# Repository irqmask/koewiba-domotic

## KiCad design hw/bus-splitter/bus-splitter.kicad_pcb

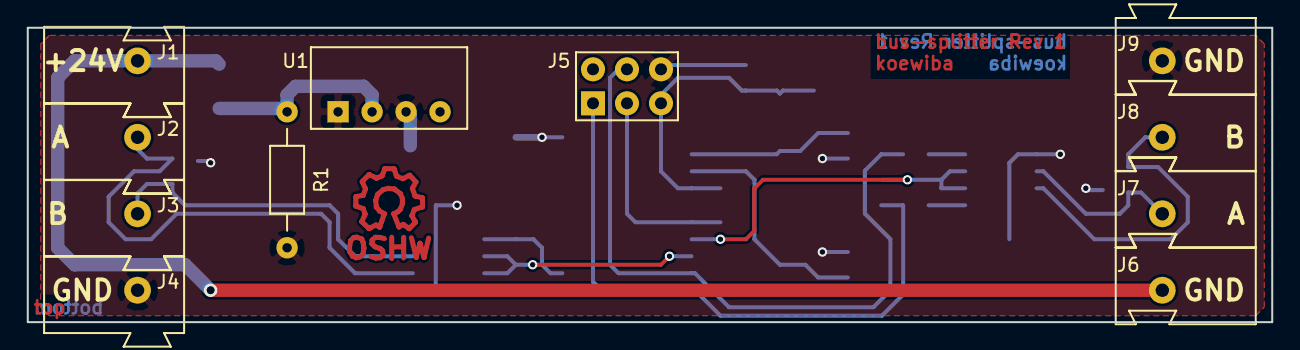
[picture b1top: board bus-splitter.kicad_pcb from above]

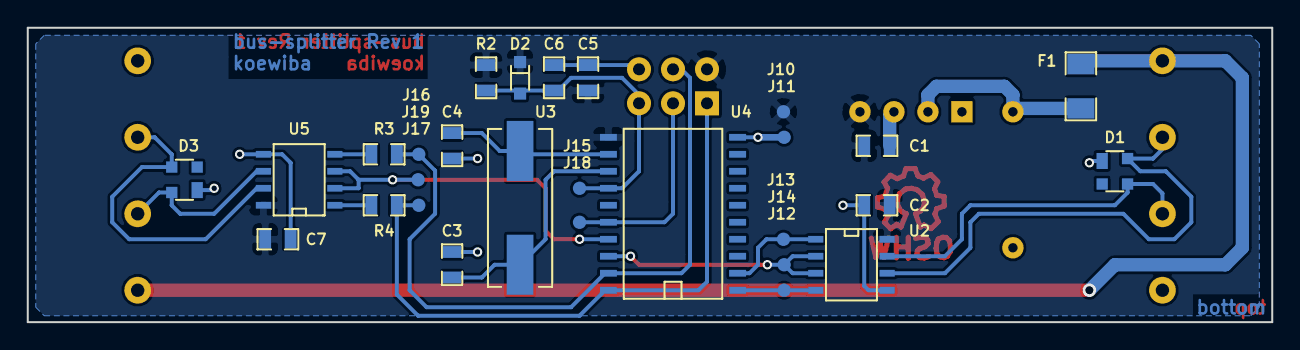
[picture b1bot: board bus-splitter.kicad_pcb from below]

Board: 2 copper layers, 93.0 x 22.0 mm, 40 parts (28 on the bottom side), 20 nets.

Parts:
C1: 100µF/6V; C_0805
C2, C5, C7: 100nF; C_0805
C3, C4: 18pF; C_0805
C6: 4,7nF; C_0805
D1, D3: SEMTECH_SR05; D_SOT143
D2: 1N4148; D_SOD323
F1: 0,15A; R_1206
J1, J6: WAGO 243-723; WAGO243
J2, J7: WAGO 243-724; WAGO243
J3, J8: WAGO 243-721; WAGO243
J4, J9: WAGO 243-722; WAGO243
J5: CONN-ISP-6; HEADER_3x2
J10: tp_vcc; Testpoint_1mm
J11: tp_gnd; Testpoint_1mm
J12: tp_txd0; Testpoint_1mm
J13: tp_rxd0; Testpoint_1mm
J14: tp_txden0; Testpoint_1mm
J15: tp_reset; Testpoint_1mm
J16: tp_txd1_mosi; Testpoint_1mm
J17: tp_rxd1_miso; Testpoint_1mm
J18: tp_sck; Testpoint_1mm
J19: tp_txden1; Testpoint_1mm
LOGO1: OPEN_HARDWARE_1; Symbol_OSHW-Logo_Copper
R1: Varistor; R_RM10.16mm
R2: 10k; R_0805
R3, R4: 100; R_0805
U1: AM1S-2405; AM1S-XXXX_SIL4
U2, U5: MAX487; SO8E
U3: 7.3728MHz; CRY_HC49_SMD
U4: ATTINY1634-SOIC; SO20L

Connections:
+24V: F1.1, R1.1, U1.2
/24V_UNFUSED: F1.2, J1.1, J6.1
//RESET: C6.1, D2.1, J5.5, J15.1, R2.2, U4.14
/A0: D1.4, J2.1, U2.6
/A1: D3.4, J7.1, U5.6
/B0: D1.3, J3.1, U2.7
/B1: D3.3, J8.1, U5.7
/RXD0: J13.1, U2.1, U4.2
/RXD1_MISO: J5.1, J17.1, R4.1, U4.20
/SCK: J5.3, J18.1, U4.16
/TXD0: J12.1, U2.4, U4.1
/TXD1_MOSI: J5.4, J16.1, R3.1, U4.19
/TXDEN0: J14.1, U2.2, U2.3, U4.18
/TXDEN1: J19.1, U4.17, U5.2, U5.3
GND: C1.2, C2.1, C3.2, C4.2, C5.1, C6.2, C7.1, D1.1, D3.1, J4.1, J5.6, J9.1, J11.1, R1.2, U1.1, U1.3, U2.5, U4.10, U5.5
unnamed: C3.1, U3.2, U4.13
unnamed: C4.1, U3.1, U4.12
unnamed: R3.2, U5.4
unnamed: R4.2, U5.1
VCC: C1.1, C2.2, C5.2, C7.2, D2.2, J5.2, J10.1, R2.1, U1.4, U2.8, U4.11, U5.8

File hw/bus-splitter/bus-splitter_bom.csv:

"Id";"Bezeichner";"Gehäuse";"Stückzahl";"Bezeichnung";"Anbieter und Ref";
1;"U1";"AM1S-XXXX_SIL4";1;"AM1S-2405";;;
2;"J1,J6";"WAGO243";2;"WAGO 243-723";;;
3;"J2,J7";"WAGO243";2;"WAGO 243-724";;;
4;"J3,J8";"WAGO243";2;"WAGO 243-721";;;
5;"J4,J9";"WAGO243";2;"WAGO 243-722";;;
6;"C1";"C_0805";1;"100µF/6V";;;
7;"C2,C5,C7";"C_0805";3;"100nF";;;
8;"C3,C4";"C_0805";2;"18pF";;;
9;"C6";"C_0805";1;"4,7nF";;;
10;"D1,D3";"D_SOT143";2;"SEMTECH_SR05";;;
11;"D2";"D_SOD323";1;"1N4148";;;
12;"F1";"R_1206";1;"0,15A";;;
13;"J5";"HEADER_3x2";1;"CONN-ISP-6";;;
14;"R1";"R_RM10.16mm";1;"Varistor";;;
15;"R2";"R_0805";1;"10k";;;
16;"R3,R4";"R_0805";2;"100";;;
17;"U2,U5";"SO8E";2;"MAX487";;;
18;"U3";"CRY_HC49_SMD";1;"7.3728MHz";;;
19;"U4";"SO20L";1;"ATTINY1634-SOIC";;;
20;"LOGO1";"Symbol_OSHW-Logo_Copper";1;"OPEN_HARDWARE_1";;;
21;"J10";"Testpoint_1mm";1;"tp_vcc";;;
22;"J11";"Testpoint_1mm";1;"tp_gnd";;;
23;"J12";"Testpoint_1mm";1;"tp_txd0";;;
24;"J13";"Testpoint_1mm";1;"tp_rxd0";;;
25;"J14";"Testpoint_1mm";1;"tp_txden0";;;
26;"J15";"Testpoint_1mm";1;"tp_reset";;;
27;"J16";"Testpoint_1mm";1;"tp_txd1_mosi";;;
28;"J17";"Testpoint_1mm";1;"tp_rxd1_miso";;;
29;"J18";"Testpoint_1mm";1;"tp_sck";;;
30;"J19";"Testpoint_1mm";1;"tp_txden1";;;

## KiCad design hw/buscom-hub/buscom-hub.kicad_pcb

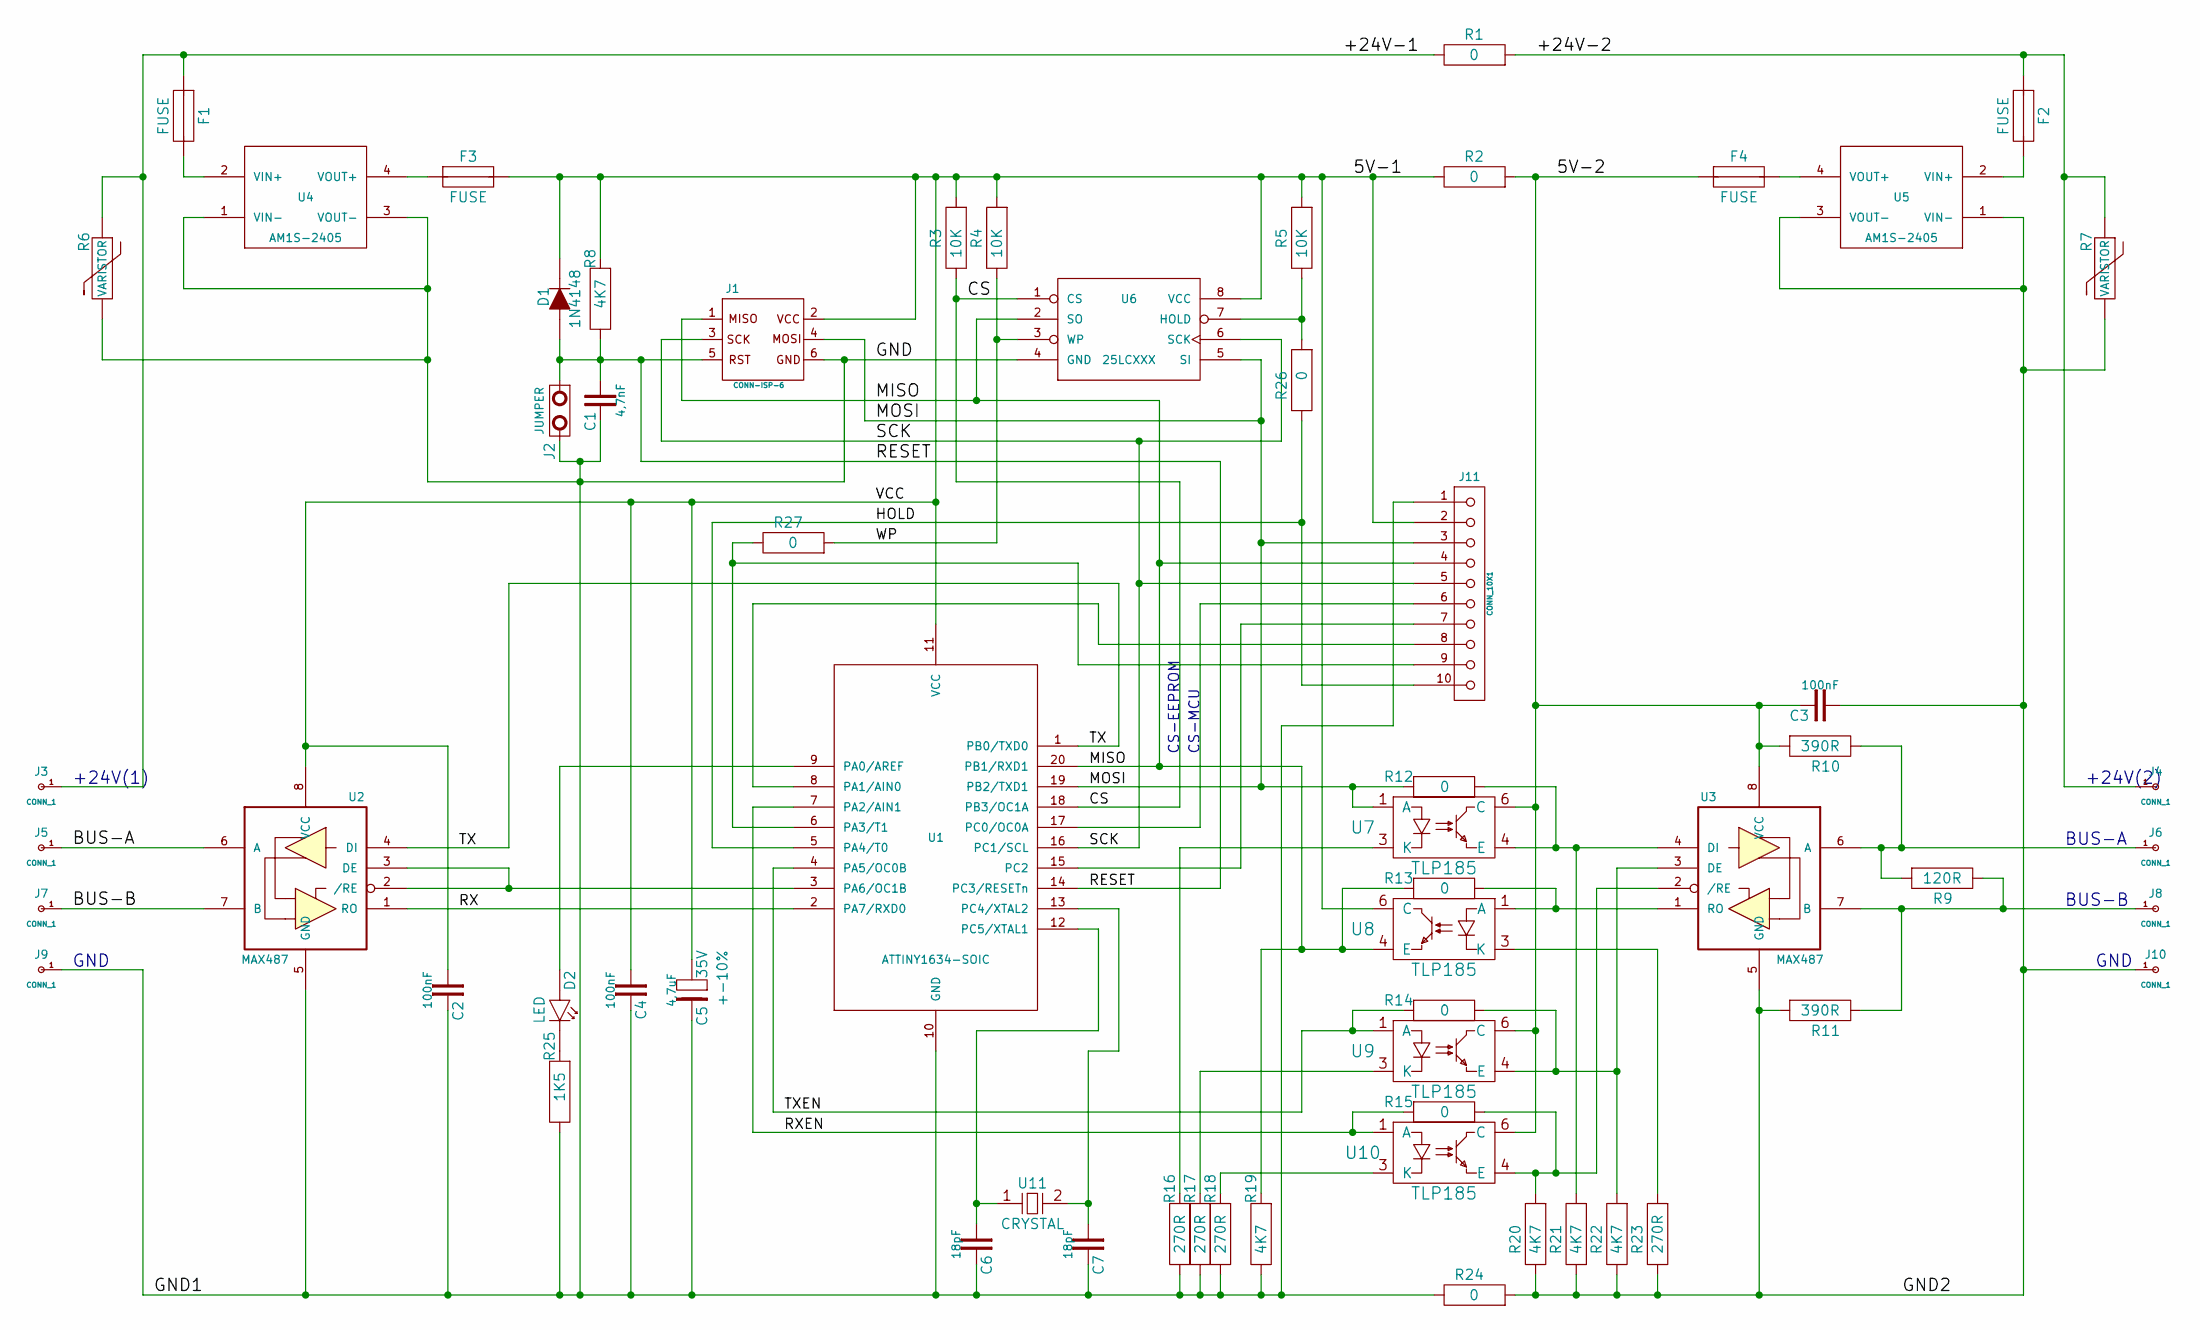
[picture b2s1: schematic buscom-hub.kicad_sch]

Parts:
C1: 4,7nF
C2, C3, C4: 100nF
C5: 4,7uF; 35V
C6, C7: 18pF
D1: 1N4148
D2: LED
F1, F2, F3, F4: FUSE
J1: CONN-ISP-6; AVR-ISP-6
J2: JUMPER
J3, J4, J5, J6, J7, J8, J9, J10: CONN_1
J11: CONN_10X1
R1, R2, R12, R13, R14, R15, R24, R26, R27: 0
R3, R4, R5: 10K
R6, R7: VARISTOR
R8, R19, R20, R21, R22: 4K7
R9: 120R
R10, R11: 390R
R16, R17, R18, R23: 270R
R25: 1K5
U1: ATTINY1634-SOIC; SO20L
U2, U3: MAX487; SSOP28
U4, U5: AM1S-2405; AM1S-XXXX_SIL4
U6: 25LCXXX; SO8N
U7, U8, U9, U10: TLP185
U11: CRYSTAL

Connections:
/5V-2: C3.2, F4.1, R2.1, R10.1, U3.8 (VCC), U7.6 (C), U9.6 (C), U10.6 (C)
/+24V-1: F1.1, J3.1, R1.2, R6.1
/+24V-2: F2.1, J4.1, R1.1, R7.1
/BUS-A: J5.1, U2.6 (A)
/BUS-B: J7.1, U2.7 (B)
/CS: R3.2, U1.18 (PB3/OC1A), U6.1 (CS)
/GND1: C1.2, C2.2, C4.1, C5.2, C6.2, C7.2, J1.6, J2.2, J9.1, J11.1, R6.2, R16.2, R17.2, R18.2, R19.2, R24.2, R25.2, U1.10 (GND), U2.5 (GND), U4.1 (VIN-), U4.3 (VOUT-), U6.4 (GND)
/GND2: C3.1, J10.1, R7.2, R11.1, R20.2, R21.2, R22.2, R23.2, R24.1, U3.5 (GND), U5.1 (VIN-), U5.3 (VOUT-)
/HOLD: J11.10, R26.2, U1.5 (PA4/T0)
/MISO: J1.1, J11.4, R13.1, R19.1, U1.20 (PB1/RXD1), U6.2 (SO), U8.4 (E)
/MOSI: J1.4, J11.3, R12.1, U1.19 (PB2/TXD1), U6.5 (SI), U7.1 (A)
/RESET: C1.1, D1.1 (A), J1.5, J2.1, R8.2, U1.14 (PC3/RESETn)
/RX: U1.2 (PA7/RXD0), U2.1 (RO)
/RXEN: R15.1, U1.7 (PA2/AIN1), U10.1 (A)
/SCK: J1.3, J11.5, U1.16 (PC1/SCL), U6.6 (SCK)
/TX: U1.1 (PB0/TXD0), U2.4 (DI)
/TXEN: R14.1, U1.4 (PA5/OC0B), U9.1 (A)
/VCC: C2.1, C4.2, C5.1, D1.2 (C), F3.2, J1.2, J11.2, R2.2, R3.1, R4.1, R5.1, R8.1, U1.11 (VCC), U2.8 (VCC), U6.8 (VCC), U8.6 (C)
/WP: R4.2, R27.1, U6.3 (WP)
unnamed: F4.2, U5.4 (VOUT+)
unnamed: D2.2 (C), R25.1
unnamed: J11.8, U1.8 (PA1/AIN0)
unnamed: R14.2, R22.1, U3.3 (DE), U9.4 (E)
unnamed: R18.1, U10.3 (K)
unnamed: R15.2, R20.1, U3.2 (/RE), U10.4 (E)
unnamed: D2.1 (A), U1.9 (PA0/AREF)
unnamed: F1.2, U4.2 (VIN+)
unnamed: F2.2, U5.2 (VIN+)
unnamed: J8.1, R9.2, R11.2, U3.7 (B)
unnamed: C6.1, U1.12 (PC5/XTAL1), U11.1
unnamed: F3.1, U4.4 (VOUT+)
unnamed: R17.1, U9.3 (K)
unnamed: R16.1, U7.3 (K)
unnamed: R23.1, U8.3 (K)
unnamed: J11.6, U1.17 (PC0/OC0A)
unnamed: J11.7, U1.15 (PC2)
unnamed: R12.2, R21.1, U3.4 (DI), U7.4 (E)
unnamed: R5.2, R26.1, U6.7 (HOLD)
unnamed: J11.9, R27.2, U1.6 (PA3/T1)
unnamed: R13.2, U3.1 (RO), U8.1 (A)
unnamed: C7.1, U1.13 (PC4/XTAL2), U11.2
unnamed: U1.3 (PA6/OC1B), U2.2 (/RE), U2.3 (DE)
unnamed: J6.1, R9.1, R10.2, U3.6 (A)

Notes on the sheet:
GND
CS-EEPROM
CS-MCU
BUS-A
BUS-B
+24V(2)
+24V(1)

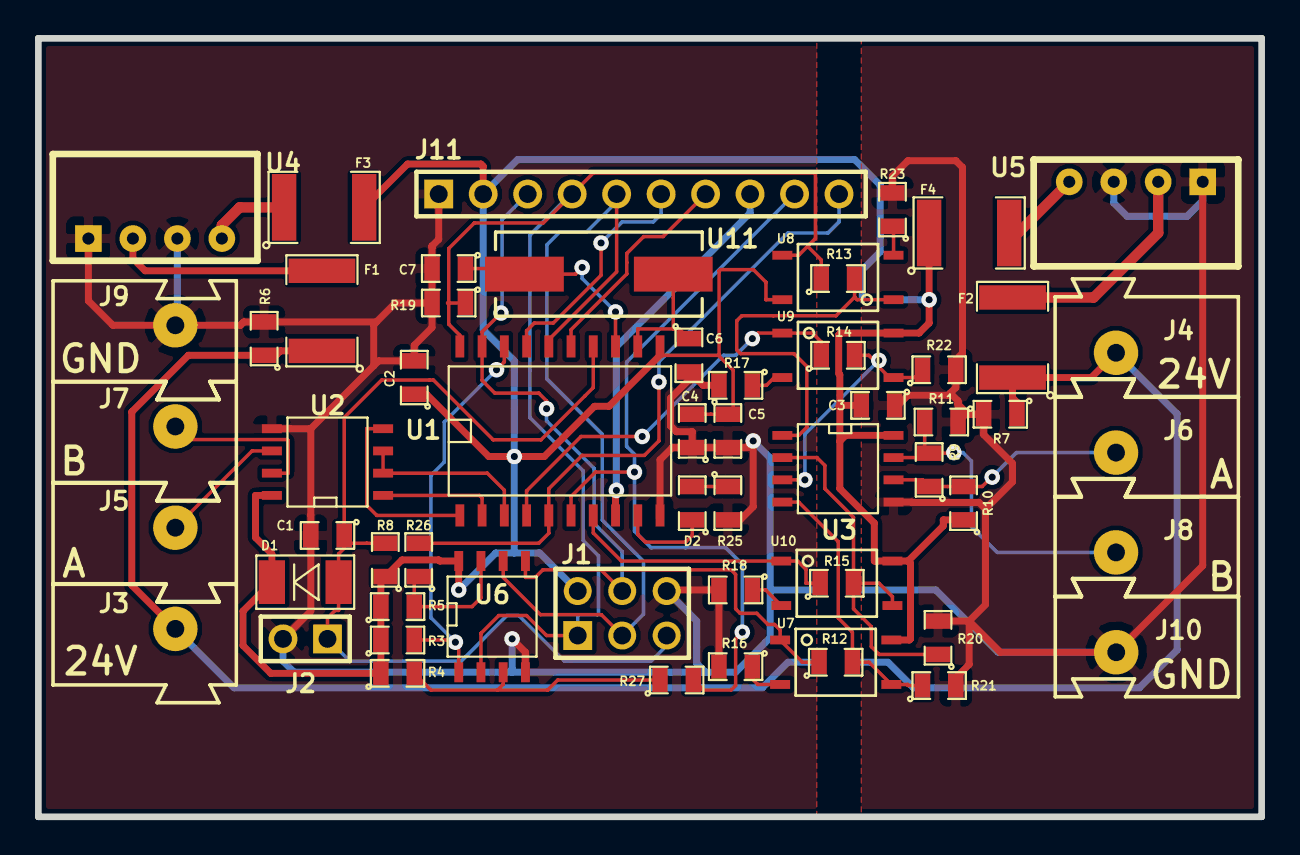
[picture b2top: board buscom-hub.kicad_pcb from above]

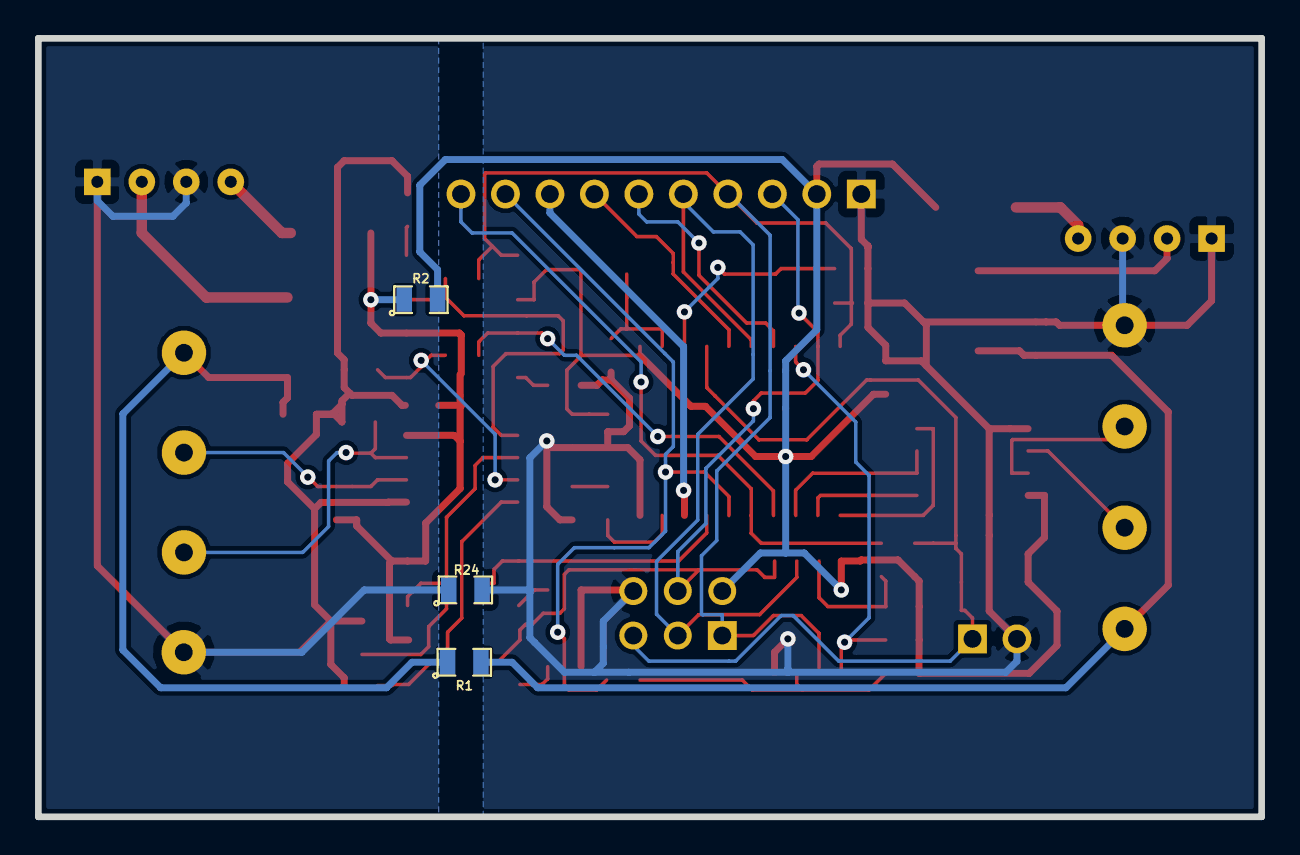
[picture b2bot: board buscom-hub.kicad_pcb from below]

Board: 2 copper layers, 69.8 x 44.4 mm, 62 parts (3 on the bottom side), 43 nets.

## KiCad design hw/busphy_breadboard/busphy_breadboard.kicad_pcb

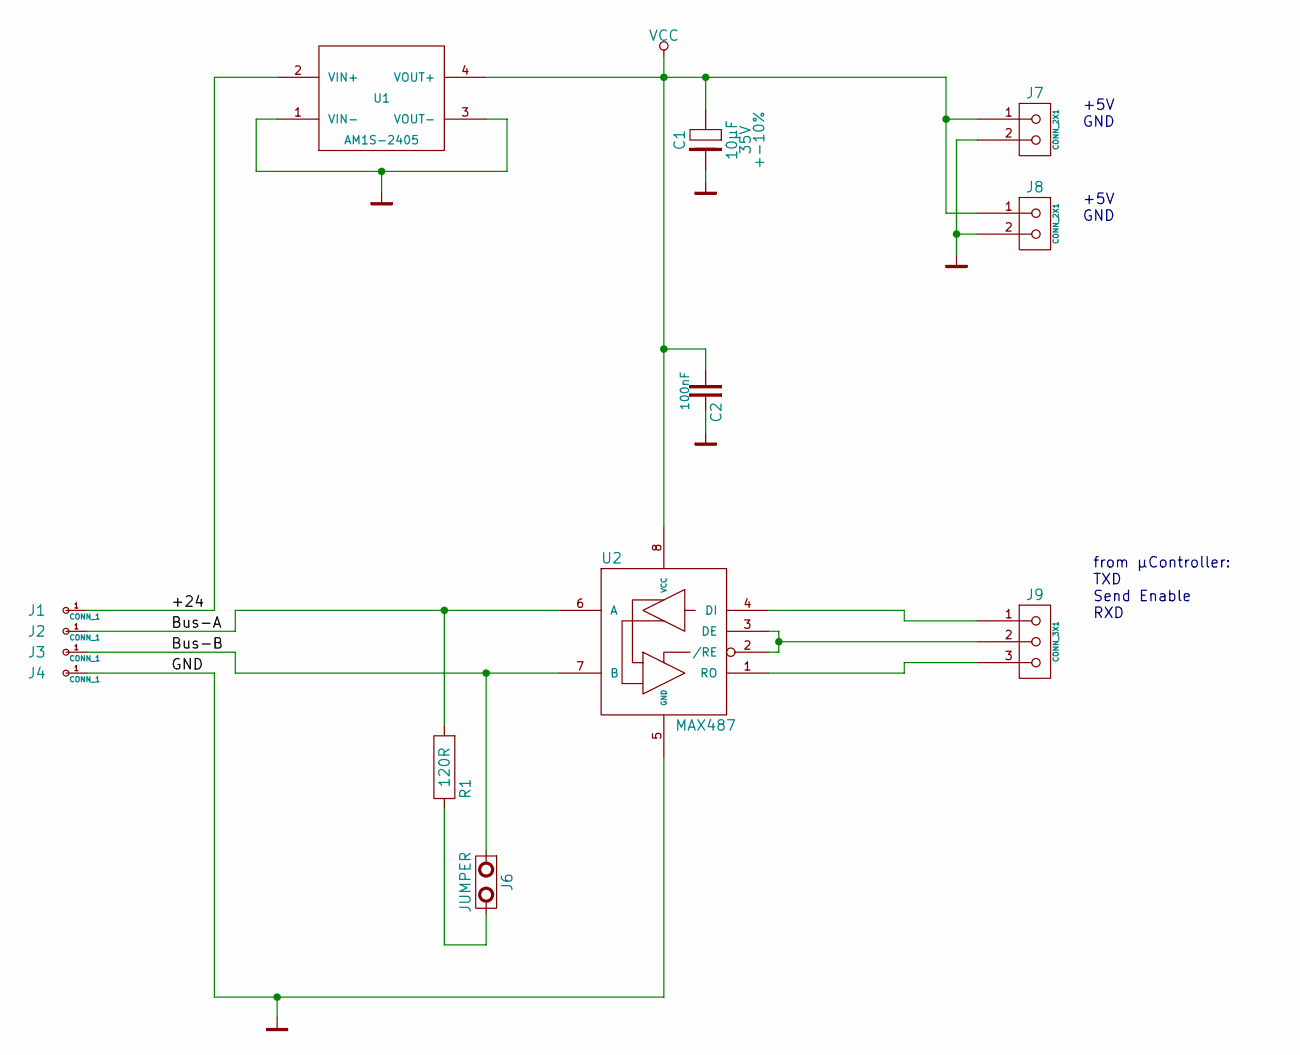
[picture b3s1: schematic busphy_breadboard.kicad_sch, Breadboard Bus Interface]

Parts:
C1: 10µF; Voltage 35V
C2: 100nF
J1, J2, J3, J4: CONN_1
J6: JUMPER
J7, J8: CONN_2X1
J9: CONN_3X1
R1: 120R
U1: AM1S-2405; AM1S-XXXX_SIL4
U2: MAX487; SSOP28

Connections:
/+24: J1.1, U1.2 (VIN+)
/Bus-A: J2.1, R1.1, U2.6 (A)
/Bus-B: J3.1, J6.1, U2.7 (B)
GND: C1.2, C2.2, J4.1, J7.2, J8.2, U1.1 (VIN-), U1.3 (VOUT-), U2.5 (GND)
unnamed: J9.2, U2.2 (/RE), U2.3 (DE)
unnamed: J9.3, U2.1 (RO)
unnamed: J9.1, U2.4 (DI)
unnamed: J6.2, R1.2
VCC: C1.1, C2.1, J7.1, J8.1, U1.4 (VOUT+), U2.8 (VCC)

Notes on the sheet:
from µController: TXD Send Enable RXD
+5V GND

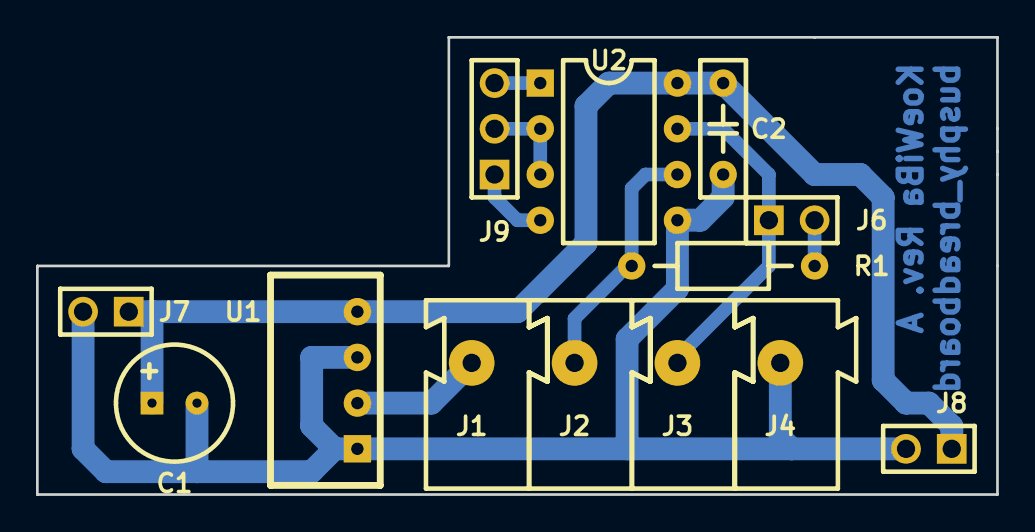
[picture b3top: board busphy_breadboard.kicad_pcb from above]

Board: 2 copper layers, 53.3 x 25.4 mm, 13 parts (0 on the bottom side), 9 nets.

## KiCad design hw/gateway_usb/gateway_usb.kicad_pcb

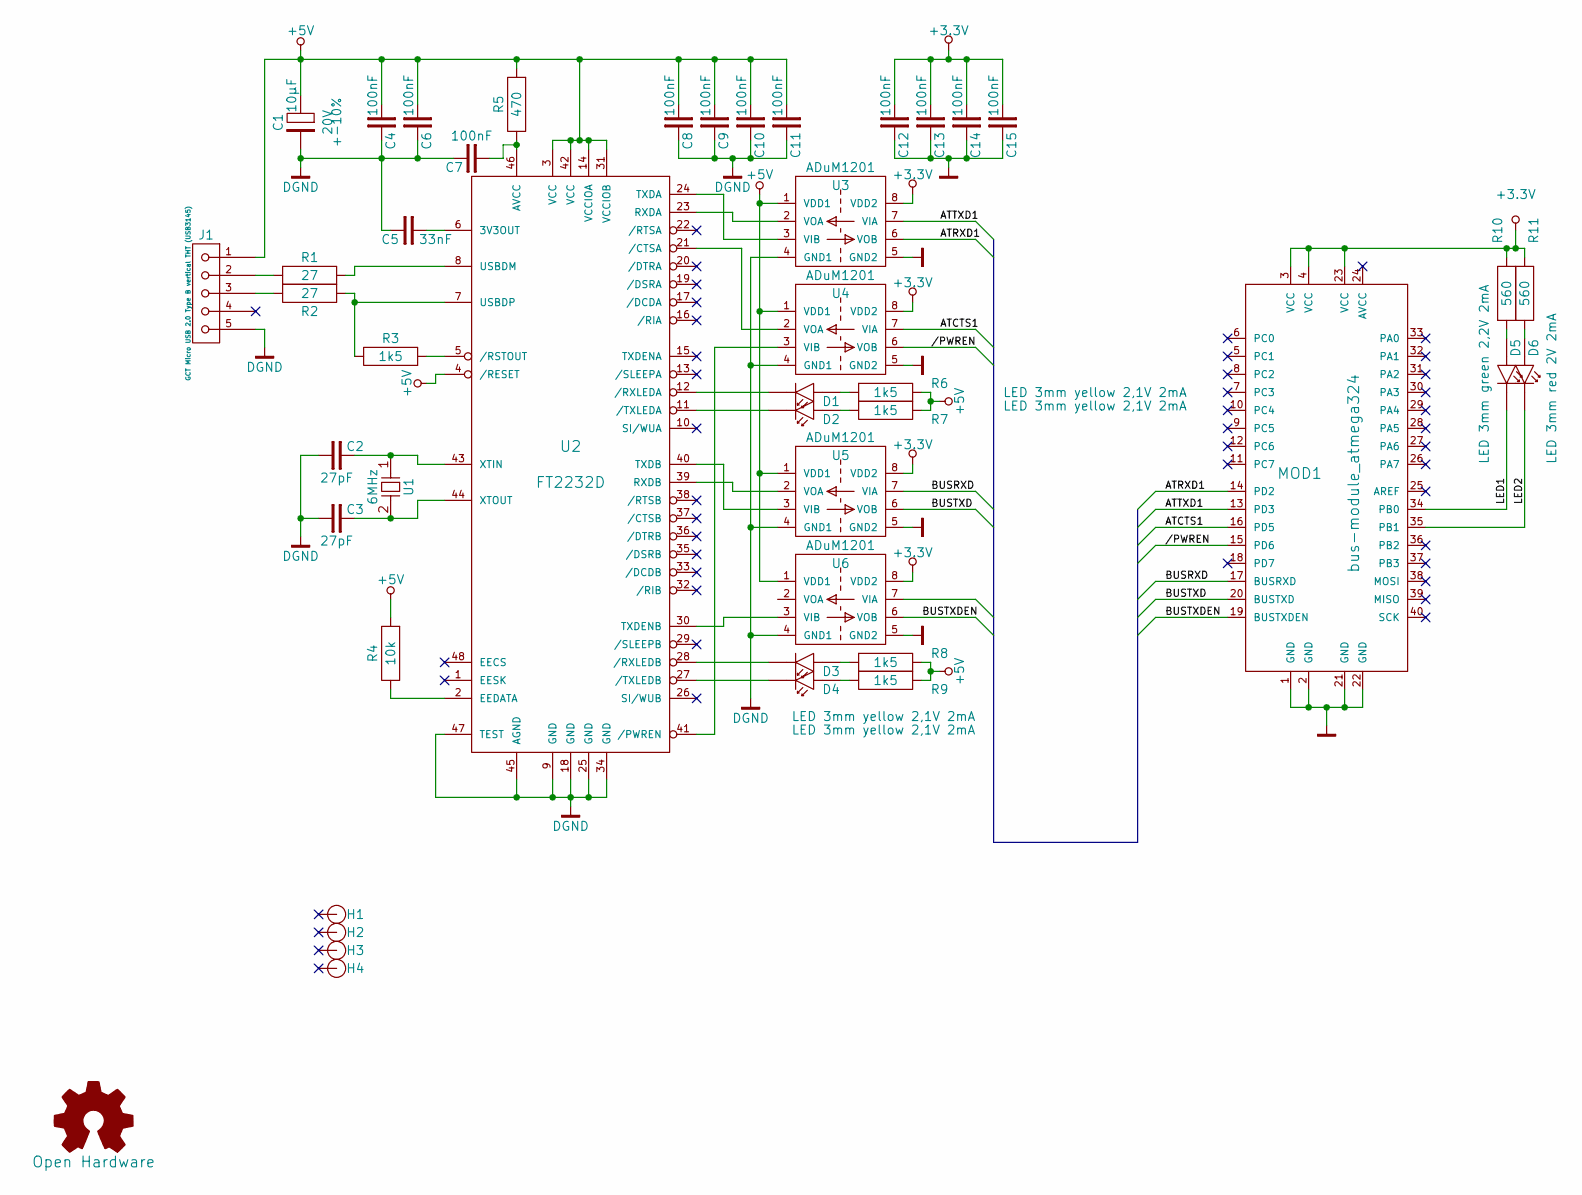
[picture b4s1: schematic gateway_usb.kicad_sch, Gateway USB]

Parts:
C1: 10µF; cp_smd_6.3; Voltage 20V
C2, C3: 27pF; SM0805
C4, C6, C7, C8, C9, C10, C11, C12, C13, C14, C15: 100nF; SM0805
C5: 33nF; SM0805
D1, D2, D3, D4: LED 3mm yellow 2,1V 2mA; LED_3MM
D5: LED 3mm green 2,2V 2mA; LED_3MM
D6: LED 3mm red 2V 2mA; LED_3MM
H1, H2, H3, H4: HOLE; HOLE_3.5x7mm
J1: GCT Micro USB 2.0 Type B vertical THT (USB3145); USB2.0_micro_THT_vertical_GCT_USB3145
LOGO1: Open Hardware; Symbol_OSHW-Logo_SilkScreen
MOD1: bus-module_atmega324
R1, R2: 27; SM0805
R3, R6, R7, R8, R9: 1k5; SM0805
R4: 10k; SM0805
R5: 470; SM0805
R10, R11: 560; SM0805
U1: 6MHz; HC49-SMD
U2: FT2232D; LQFP-48_7x7mm_Pitch0.5mm
U3, U4, U5, U6: ADuM1201; SO8E

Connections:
+3.3V: C12.1, C13.1, C14.1, C15.1, MOD1.3 (VCC), MOD1.4 (VCC), MOD1.23 (VCC), R10.2, R11.2, U3.8 (VDD2), U4.8 (VDD2), U5.8 (VDD2), U6.8 (VDD2)
+5V: C1.1, C4.1, C6.1, C8.1, C9.1, C10.1, C11.1, J1.1, R4.1, R5.1, R6.2, R7.2, R8.2, R9.2, U2.3 (VCC), U2.4 (/RESET), U2.14 (VCCIOA), U2.31 (VCCIOB), U2.42 (VCC), U3.1 (VDD1), U4.1 (VDD1), U5.1 (VDD1), U6.1 (VDD1)
//PWREN: MOD1.15 (PD6), U4.6 (VOB)
/ATCTS1: MOD1.16 (PD5), U4.7 (VIA)
/ATRXD1: MOD1.14 (PD2), U3.6 (VOB)
/ATTXD1: MOD1.13 (PD3), U3.7 (VIA)
/BUSRXD: MOD1.17 (BUSRXD), U5.7 (VIA)
/BUSTXD: MOD1.20 (BUSTXD), U5.6 (VOB)
/BUSTXDEN: MOD1.19 (BUSTXDEN), U6.6 (VOB)
/LED1: D5.2 (C), MOD1.34 (PB0)
/LED2: D6.2 (C), MOD1.35 (PB1)
DGND: C1.2, C2.1, C3.1, C4.2, C5.2, C6.2, C7.1, C8.2, C9.2, C10.2, C11.2, J1.5, U2.9 (GND), U2.18 (GND), U2.25 (GND), U2.34 (GND), U2.45 (AGND), U2.47 (TEST), U3.4 (GND1), U4.4 (GND1), U5.4 (GND1), U6.4 (GND1)
GND: C12.2, C13.2, C14.2, C15.2, MOD1.1 (GND), MOD1.2 (GND), MOD1.21 (GND), MOD1.22 (GND), U3.5 (GND2), U4.5 (GND2), U5.5 (GND2), U6.5 (GND2)
unnamed: C2.2, U1.1, U2.43 (XTIN)
unnamed: C3.2, U1.2, U2.44 (XTOUT)
unnamed: C5.1, U2.6 (3V3OUT)
unnamed: C7.2, R5.2, U2.46 (AVCC)
unnamed: D1.1 (A), R6.1
unnamed: D1.2 (C), U2.12 (/RXLEDA)
unnamed: D2.1 (A), R7.1
unnamed: D2.2 (C), U2.11 (/TXLEDA)
unnamed: D3.1 (A), R8.1
unnamed: D3.2 (C), U2.28 (/RXLEDB)
unnamed: D4.1 (A), R9.1
unnamed: D4.2 (C), U2.27 (/TXLEDB)
unnamed: D5.1 (A), R10.1
unnamed: D6.1 (A), R11.1
unnamed: J1.2, R1.1
unnamed: J1.3, R2.1
unnamed: R1.2, U2.8 (USBDM)
unnamed: R2.2, R3.2, U2.7 (USBDP)
unnamed: R3.1, U2.5 (/RSTOUT)
unnamed: R4.2, U2.2 (EEDATA)
unnamed: U2.21 (/CTSA), U4.2 (VOA)
unnamed: U2.23 (RXDA), U3.2 (VOA)
unnamed: U2.24 (TXDA), U3.3 (VIB)
unnamed: U2.30 (TXDENB), U6.3 (VIB)
unnamed: U2.39 (RXDB), U5.2 (VOA)
unnamed: U2.40 (TXDB), U5.3 (VIB)
unnamed: U2.41 (/PWREN), U4.3 (VIB)

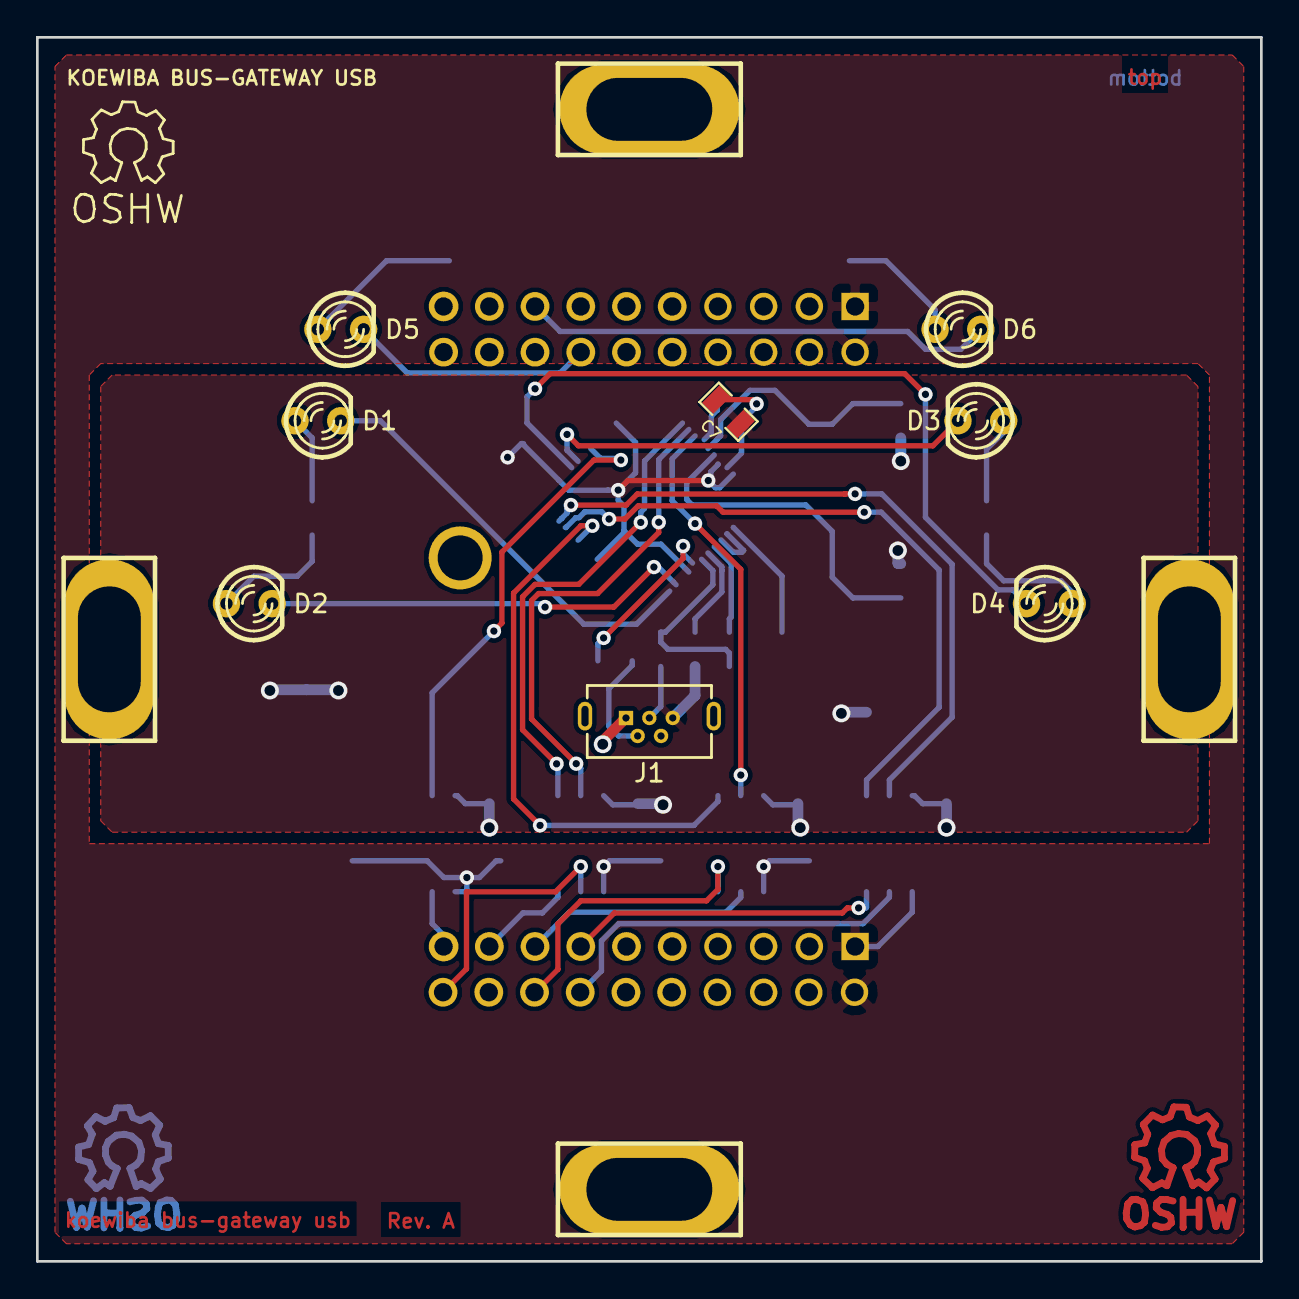
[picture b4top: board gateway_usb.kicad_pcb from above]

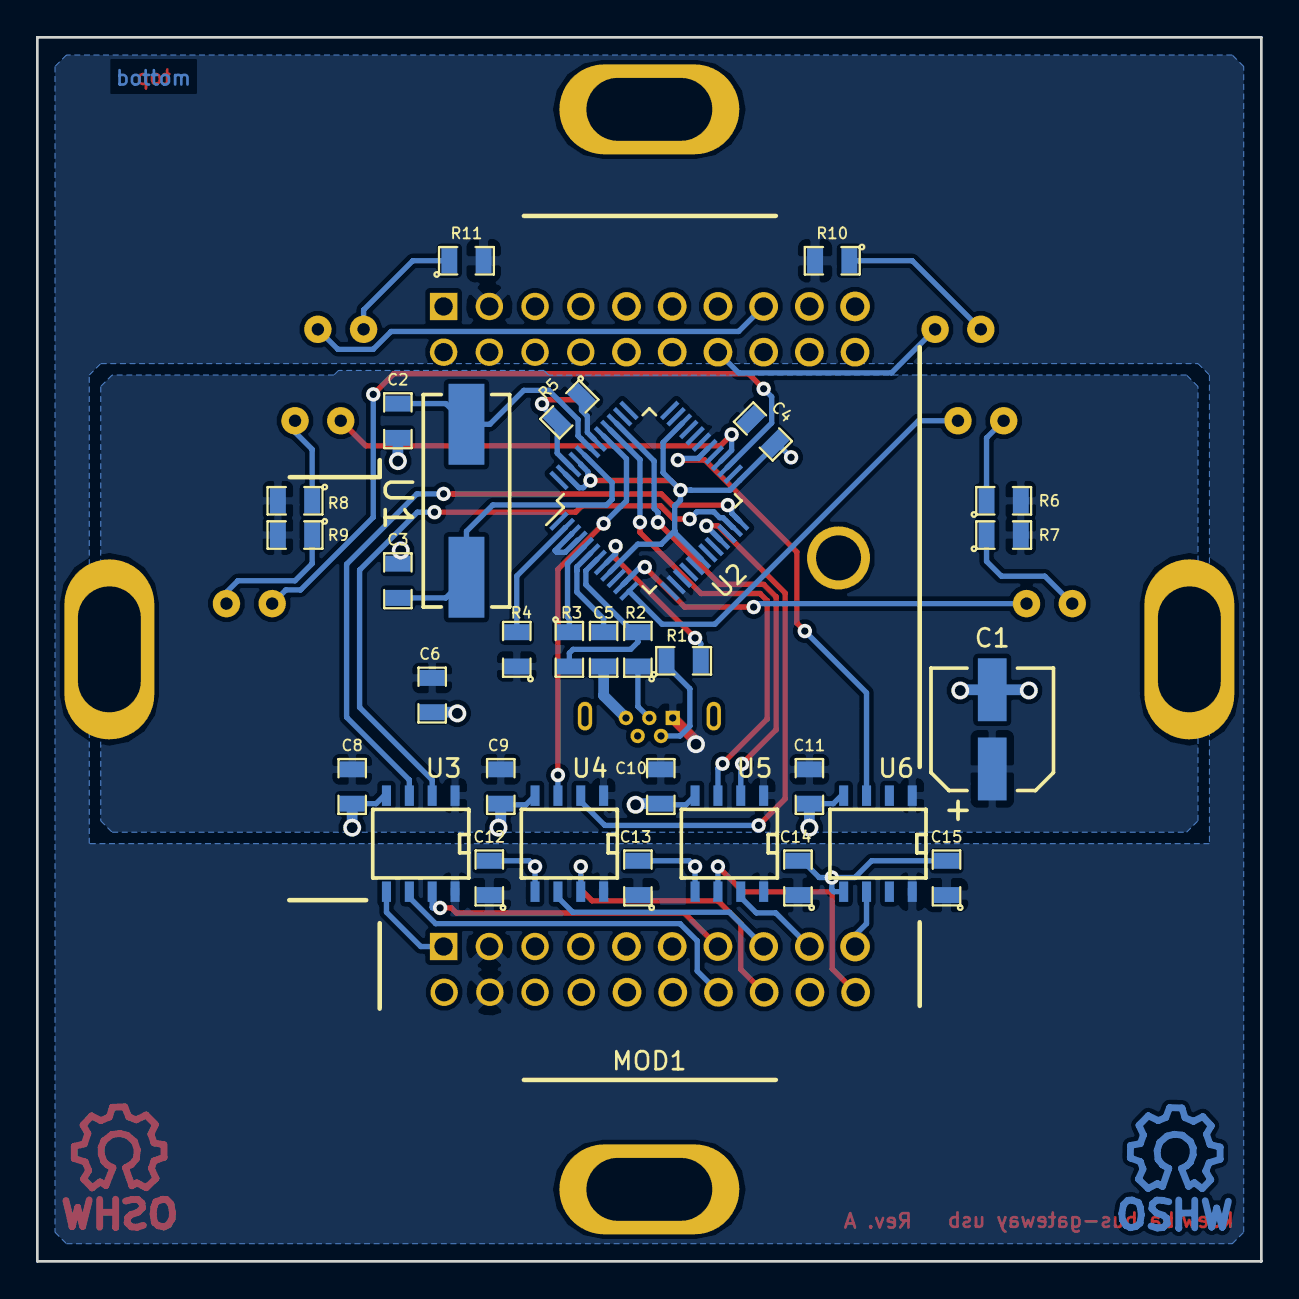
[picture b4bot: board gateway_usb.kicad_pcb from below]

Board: 2 copper layers, 68.0 x 68.0 mm, 47 parts (33 on the bottom side), 40 nets.

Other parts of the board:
LOGO1#2, LOGO1#3: Open Hardware; Symbol_OSHW-Logo_Copper

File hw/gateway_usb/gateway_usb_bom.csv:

Bezeichner,Gehäuse,Stückzahl,Bezeichnung,Anbieter und Ref
C1,cp_smd_6.3,1,10µF,
"C4,C6,C7,C8,C9,C10,C11,C12,C13,C14,C15",SM0805,4,100nF,
"C2,C3",SM0805,2,27pF,
C5,SM0805,1,33nF,
"D1,D2,D3,D4",LED_3MM,4,"LED 3mm yellow 2,1V 2mA",
D5,LED_3MM,1,"LED 3mm green 2,2V 2mA",
D6,LED_3MM,1,LED 3mm red 2V 2mA,
J1,USB2.0_micro_THT_vertical_GCT_USB3145,1,GCT Micro USB 2.0 Type B vertical THT (USB3145),
MOD1,bus-module_atmega324,1,bus-module_atmega324,
"R1,R2",SM0805,2,27,
"R10,R11",SM0805,2,560,
"R3,R6,R7,R8,R9",SM0805,5,1k5,
R4,SM0805,1,10k,
R5,SM0805,1,470,
U1,HC49-SMD,1,6MHz,
U2,LQFP-48_7x7mm_Pitch0.5mm,1,FT2232D,
"U3,U4,U5,U6",SO8E,4,ADuM1201,

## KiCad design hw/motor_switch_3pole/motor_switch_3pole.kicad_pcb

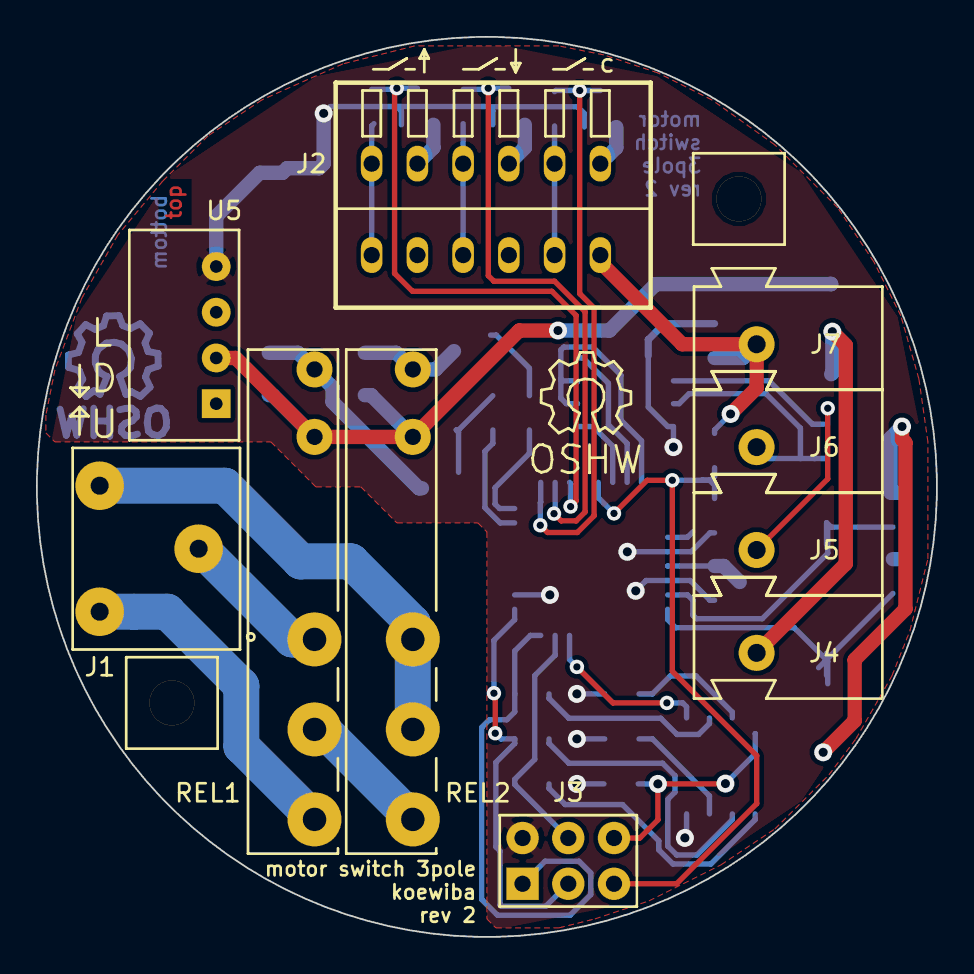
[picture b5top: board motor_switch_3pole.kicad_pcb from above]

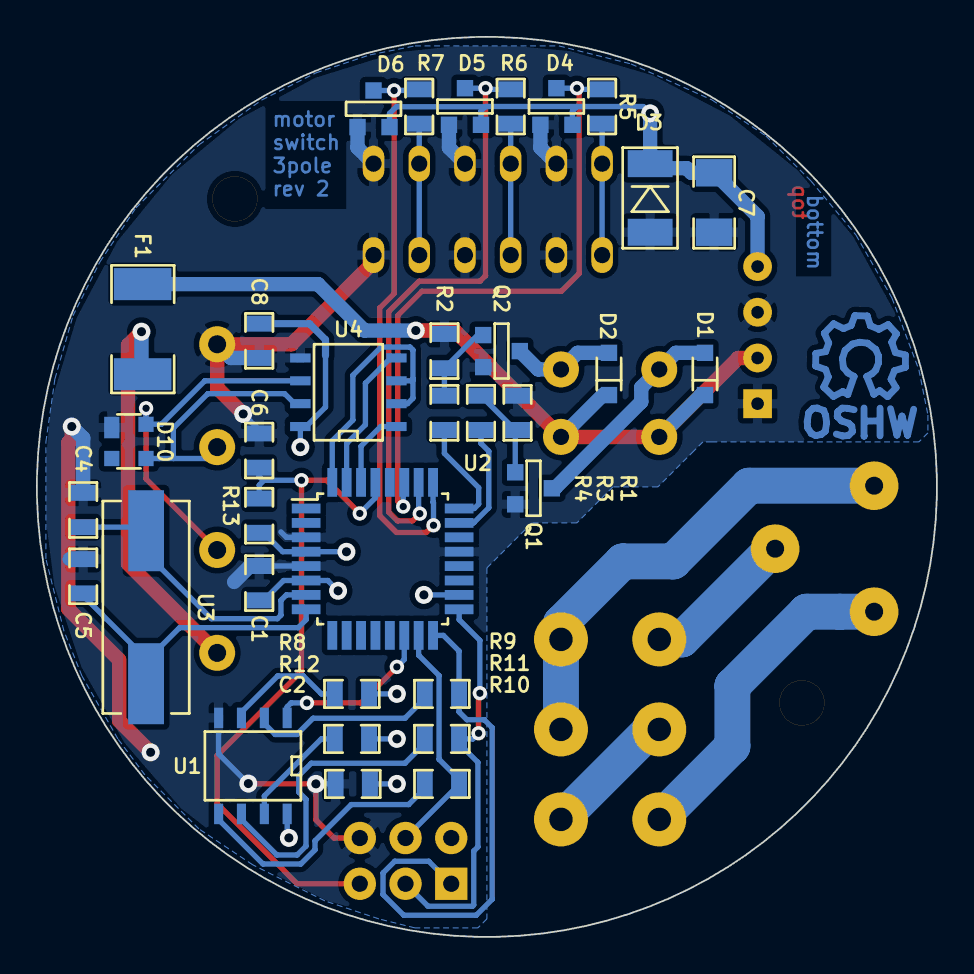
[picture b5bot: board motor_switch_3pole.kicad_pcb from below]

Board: 2 copper layers, 50.0 x 50.0 mm, 48 parts (35 on the bottom side), 37 nets.

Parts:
C1, C2, C8: 100nF; C_0805
C4, C5: 18pF; C_0805
C6: 4,7nF; C_0805
C7: 100µF / 6V; C_1206
D1, D2: 1N4148; D_SOD323
D3: ZD5V6; D_MINIMELF
D4, D5, D6: BAT54S; SOT23-3
D10: SEMTECH SR05; D_SOT143
F1: FUSE; R_1812
H1, H2: HOLE; HOLE_2.5mm_wo_Copper
J1: WAGO 2081-1123; WAGO_2081-1123
J2: WAGO 233-506; WAGO_233-6
J3: CONN-ISP-6; HEADER_3x2
J4: WAGO 243-723; WAGO_243
J5: WAGO 243-724; WAGO_243
J6: WAGO 243-721; WAGO_243
J7: WAGO 243-722; WAGO_243
LOGO1: OPEN_HARDWARE_1; Symbol_OSHW-Logo_Copper
LOGO2: Open Hardware; Symbol_OSHW-Logo_SilkScreen
Q1, Q2: BSS138; SOT23-3
R1, R2, R8, R12, R13: 10k; R_0805
R3, R4, R9, R10, R11: 100; R_0805
R5, R6, R7: 4k7; R_0805
REL1, REL2: FINDER_34.51.7.024; finder_34.51_1xUM
U1: 25LC256; SO8E
U2: ATMEGA328-TQFP32; TQFP-32_7x7mm_Pitch0.8mm
U3: 7,3728MHz; CRY_HC49_SMD
U4: MAX487ECSA; SO8E
U5: AM1S-2405; AM1S-XXXX_SIL4

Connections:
+5V: C1.1, C2.1, C7.1, C8.2, D3.2, D4.2, D5.2, D6.2, J3.2, R8.1, R12.1, R13.1, U1.8, U2.4, U2.6, U2.18, U4.8, U5.4
+24V: D1.2, D2.2, F1.1, REL1.2, REL2.2, U5.2
/230V_DOWN: J1.2, REL1.3
/230V_L: J1.3, REL2.3, REL2.4
/230V_ON: REL1.4, REL2.5
/230V_UP: J1.1, REL1.5
//button_down: D5.3, R6.1, U2.26
//button_up: D4.3, R5.1, U2.27
//switch_close: D6.3, R7.1, U2.25
/bus_atmega328_basic//CSEEP: U1.1, U2.14
/bus_atmega328_basic//RESET: C6.1, J3.5, R13.2, U2.29
/bus_atmega328_basic/A: D10.4, J5.1, U4.6
/bus_atmega328_basic/B: D10.3, J6.1, U4.7
/bus_atmega328_basic/MISO: R9.2, U1.2
/bus_atmega328_basic/MOSI: R10.2, U1.5
/bus_atmega328_basic/PB3_MOSI: J3.4, R10.1, U2.15
/bus_atmega328_basic/PB4_MISO: J3.1, R9.1, U2.16
/bus_atmega328_basic/PB5_SCK: J3.3, R11.1, U2.17
/bus_atmega328_basic/RXD0: U2.30, U4.1
/bus_atmega328_basic/SCK: R11.2, U1.6
/bus_atmega328_basic/TXD0: U2.31, U4.4
/bus_atmega328_basic/TXD0EN: U2.32, U4.2, U4.3
/relay_on: R4.2, U2.24
/relay_up: R3.2, U2.23
GND: C1.2, C2.2, C4.2, C5.2, C6.2, C7.2, C8.1, D3.1, D4.1, D5.1, D6.1, D10.1, J2.2, J2.4, J2.6, J3.6, J7.1, Q1.2, Q2.2, R1.2, R2.2, U1.4, U2.3, U2.5, U2.21, U4.5, U5.1, U5.3
unnamed: C4.1, U2.7, U3.1
unnamed: C5.1, U2.8, U3.2
unnamed: D1.1, Q1.3, REL1.1
unnamed: D2.1, Q2.3, REL2.1
unnamed: F1.2, J4.1
unnamed: J2.1, R5.2
unnamed: J2.3, R6.2
unnamed: J2.5, R7.2
unnamed: Q1.1, R1.1, R3.1
unnamed: Q2.1, R2.1, R4.1
unnamed: R8.2, U1.3
unnamed: R12.2, U1.7
